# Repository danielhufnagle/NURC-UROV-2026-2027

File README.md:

# NURC-UROV-2026-2027
Electrical and Software for MATE UROV 2026-2027
well hello there

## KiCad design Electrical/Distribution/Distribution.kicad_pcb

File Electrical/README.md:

# Electrical

Place all PCB files here. Include both component and footprint libraries as well

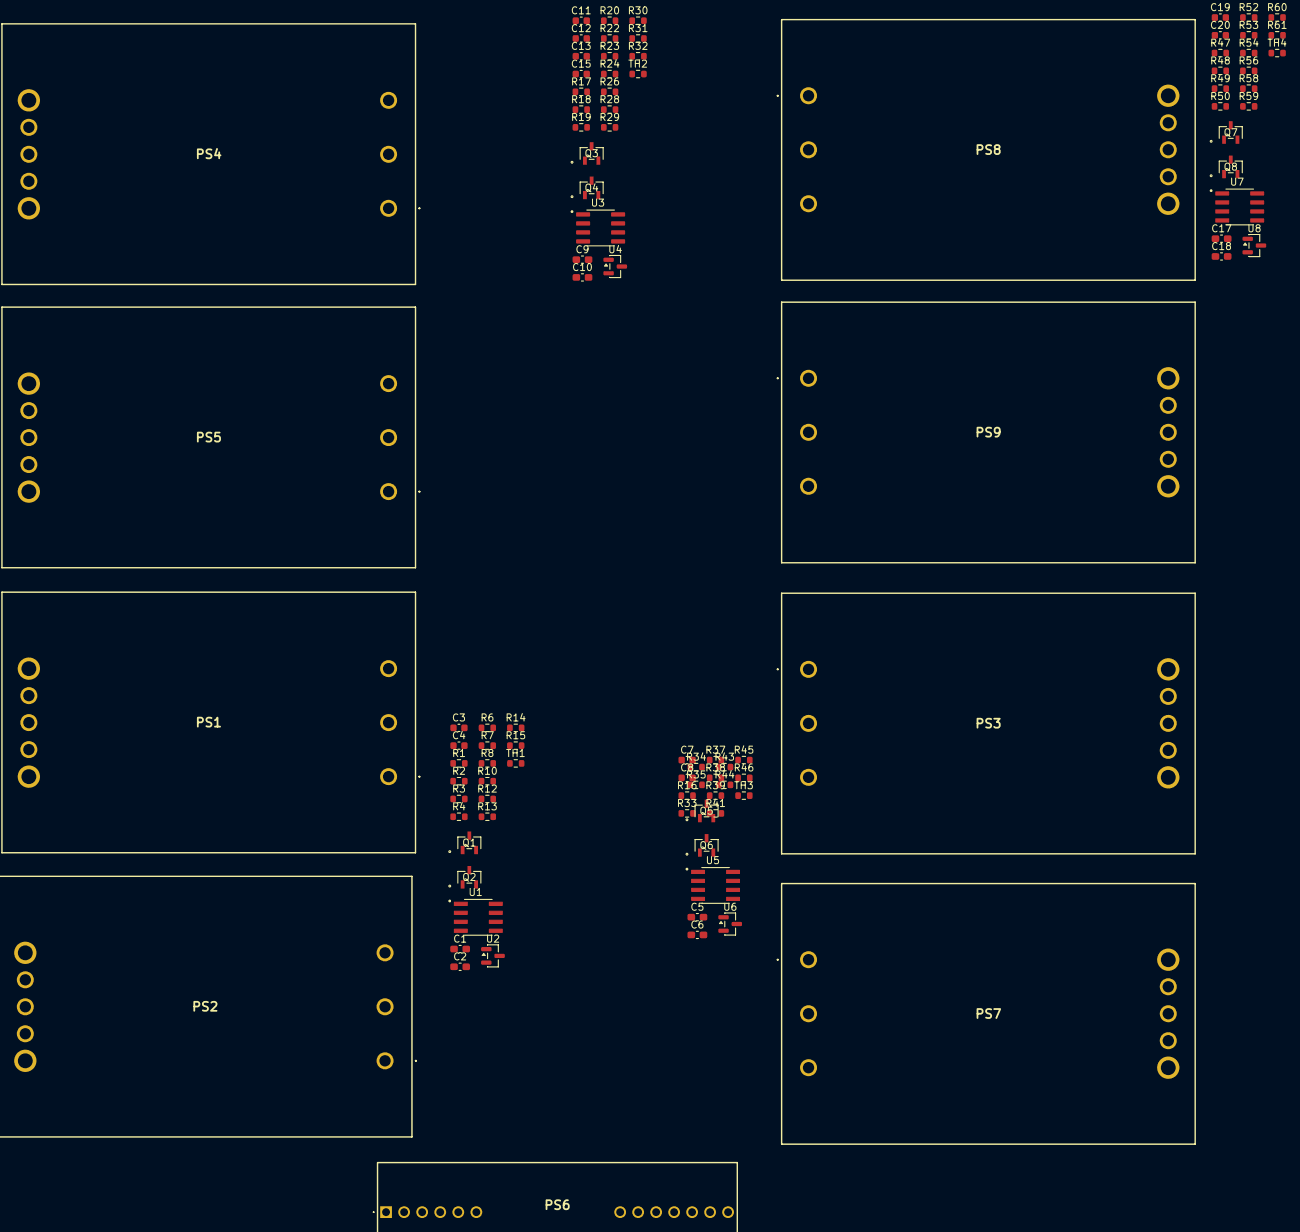
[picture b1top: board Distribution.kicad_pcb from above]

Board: 2 copper layers, 96 parts (0 on the bottom side), 48 nets, no tracks yet.

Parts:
C1, C2, C5, C6, C9, C10, C17, C18: 100uf; C_0603_1608Metric_Pad1.08x0.95mm_HandSolder
C3, C4, C7, C8, C11, C12, C19, C20: 100uf; C_0603_1608Metric
C13: 10uf; C_0603_1608Metric
C15: 100nF; C_0603_1608Metric
PS1, PS2, PS3, PS4, PS5, PS7, PS8, PS9: Q36SR12017NRFA
PS6: NID100-5; NID1005
Q1, Q2, Q3, Q4, Q5, Q6, Q7, Q8: Q_NMOS; TO-236AB_SOT23_NEX
R1, R3, R16, R17, R19, R34, R47, R49: 7k; R_0603_1608Metric
R2, R4, R13, R18, R20, R30, R33, R35, R44, R48, R50, R59: 5k; R_0603_1608Metric
R6, R7, R22, R23, R37, R38, R52, R53: 1k; R_0603_1608Metric
R8, R24, R39, R54: 50k; R_0603_1608Metric
R10, R12, R14, R15, R26, R28, R29, R31, R32, R41, R43, R45, R46, R56, R58, R60, R61: 10k; R_0603_1608Metric
TH1, TH2, TH3, TH4: Thermistor NTC 10k; R_0603_1608Metric
U1, U3, U5, U7: LM393; SOIC127P599X175-8N
U2, U4, U6, U8: LM4040DBZ-5; SOT-23

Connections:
/48-12-5/5VOut: PS6.1 (+VOUT_1), PS6.2 (+VOUT_2), PS6.3 (+VOUT_3), PS6.4 (+VOUT_4)
/48-12-5/5VRef: R22.1, R30.2, U3.8 (V+), U4.1 (K)
/48-12-5/12V: PS6.9 (+VIN_1), PS6.10 (+VIN_2)
/48-12-5/12V1: C11.2, PS4.8 (+VOUT), R19.1, R30.1, R31.1
/48-12-5/12V2: C12.2, PS5.8 (+VOUT), R17.1, R32.1
/48-12-5/48V1: C9.1, PS4.1 (+VIN)
/48-12-5/48V2: C10.1, PS5.1 (+VIN)
/48-12-5/CompOut1: R24.1, R26.2, U3.1
/48-12-5/ConvertersOn: PS4.2 (ON/OFF), PS5.2 (ON/OFF), PS6.13 (R.C.), R29.1
/48-12-5/Vtherm: R28.2, TH2.1
/48-12-5/~5Vin1: R19.2, R20.1
/48-12-5/~5Vin2: R17.2, R18.1
/48-12-inst1/5VRef: R6.1, R10.1, R13.2, U1.8 (V+), U2.1 (K)
/48-12-inst1/12V1: C3.2, PS1.8 (+VOUT), R3.1, R13.1, R14.1
/48-12-inst1/12V2: C4.2, PS2.8 (+VOUT), R1.1, R15.1
/48-12-inst1/48V: C1.1, C2.1, PS1.1 (+VIN), PS2.1 (+VIN)
/48-12-inst1/CompOut1: R8.1, R10.2, U1.1
/48-12-inst1/ConvertersOn: PS1.2 (ON/OFF), PS2.2 (ON/OFF)
/48-12-inst1/Vtherm: R12.2, TH1.1
/48-12-inst1/~5Vin1: R3.2, R4.1
/48-12-inst1/~5Vin2: R1.2, R2.1
/48-12-inst2/5VRef: R37.1, R41.1, R44.2, U5.8 (V+), U6.1 (K)
/48-12-inst2/12V1: C7.2, PS3.8 (+VOUT), R34.1, R44.1, R45.1
/48-12-inst2/12V2: C8.2, PS7.8 (+VOUT), R16.1, R46.1
/48-12-inst2/48V: C5.1, C6.1, PS3.1 (+VIN), PS7.1 (+VIN)
/48-12-inst2/CompOut1: R39.1, R41.2, U5.1
/48-12-inst2/ConvertersOn: PS3.2 (ON/OFF), PS7.2 (ON/OFF)
/48-12-inst2/Vtherm: R43.2, TH3.1
/48-12-inst2/~5Vin1: R34.2, R35.1
/48-12-inst2/~5Vin2: R16.2, R33.1
/48-12-inst3/5VRef: R52.1, R56.1, R59.2, U7.8 (V+), U8.1 (K)
/48-12-inst3/12V1: C19.2, PS8.8 (+VOUT), R49.1, R59.1, R60.1
/48-12-inst3/12V2: C20.2, PS9.8 (+VOUT), R47.1, R61.1
/48-12-inst3/48V: C17.1, C18.1, PS8.1 (+VIN), PS9.1 (+VIN)
/48-12-inst3/CompOut1: R54.1, R56.2, U7.1
/48-12-inst3/ConvertersOn: PS8.2 (ON/OFF), PS9.2 (ON/OFF)
/48-12-inst3/Vtherm: R58.2, TH4.1
/48-12-inst3/~5Vin1: R49.2, R50.1
/48-12-inst3/~5Vin2: R47.2, R48.1
GND: C1.2, C2.2, C3.1, C4.1, C5.2, C6.2, C7.1, C8.1, C9.2, C10.2, C11.1, C12.1, C13.2, C15.2, C17.2, C18.2, C19.1, C20.1, PS1.3 (-VIN), PS1.4 (-VOUT), PS2.3 (-VIN), PS2.4 (-VOUT), PS3.3 (-VIN), PS3.4 (-VOUT), PS4.3 (-VIN), PS4.4 (-VOUT), PS5.3 (-VIN), PS5.4 (-VOUT), PS6.5 (COM_1), PS6.6 (COM_2), PS6.7 (COM_3), PS6.8 (COM_4), PS7.3 (-VIN), PS7.4 (-VOUT), PS8.3 (-VIN), PS8.4 (-VOUT), PS9.3 (-VIN), PS9.4 (-VOUT), R2.2, R4.2, R18.2, R20.2, R29.2, R33.2, R35.2, R48.2, R50.2, TH1.2, TH2.2, TH3.2, TH4.2, U1.4 (V-), U2.2 (A), U3.4 (V-), U4.2 (A), U5.4 (V-), U6.2 (A), U7.4 (V-), U8.2 (A)
unnamed: R7.2, R8.2, U1.3 (+)
unnamed: R6.2, U1.2 (-)
unnamed: R23.2, R24.2, U3.3 (+)
unnamed: R22.2, U3.2 (-)
unnamed: R38.2, R39.2, U5.3 (+)
unnamed: R37.2, U5.2 (-)
unnamed: R53.2, R54.2, U7.3 (+)
unnamed: R52.2, U7.2 (-)

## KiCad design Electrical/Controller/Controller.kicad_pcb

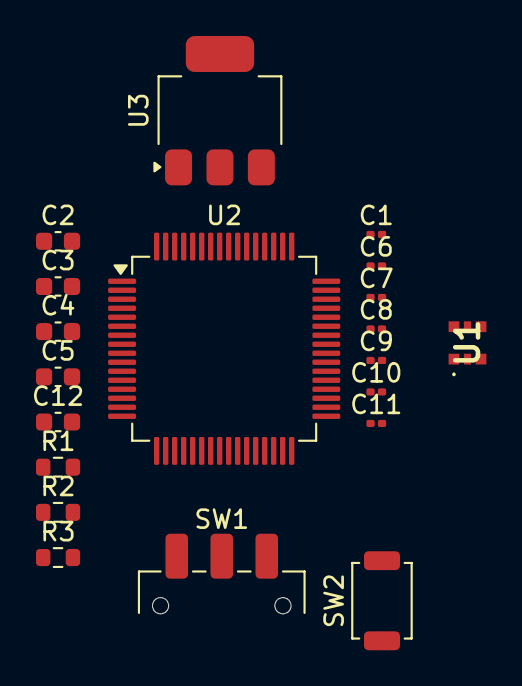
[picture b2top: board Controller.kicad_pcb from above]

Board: 2 copper layers, 20 parts (0 on the bottom side), 9 nets, no tracks yet.

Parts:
C1, C6, C7, C8, C9, C10, C11: 100nf; C_0201_0603Metric
C2, C3, C4: 10uf; C_0603_1608Metric
C5, C12: 100nf; C_0603_1608Metric
R1, R2, R3: 10k; R_0603_1608Metric
SW1: SW_SPDT; SW_SPDT_CK_JS102011SAQN
SW2: SW_SPST; SW_SPST_TS-1088-xR020
U1: 74LVC1G332; 74LVC1G332GW125
U2: STM32F446RETx; LQFP-64_10x10mm_P0.5mm
U3: AMS1117-3.3; SOT-223-3_TabPin2

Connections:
+5V: C4.1, U3.3 (VI)
/IsLeak: U1.4, U2.40 (PC9)
/LDO 3V3: C3.1, C6.1, C7.1, C8.1, C9.1, C10.1, C11.1, C12.2, R1.1, R3.1, U1.5 (VCC), U2.1 (VBAT), U2.13 (VDDA), U2.19 (VDD), U2.32 (VDD), U2.48 (VDD), U2.64 (VDD), U3.2 (VO)
GND: C1.2, C2.2, C3.2, C4.2, C5.1, C6.2, C7.2, C8.2, C9.2, C10.2, C11.2, C12.1, R2.2, SW2.1 (A), U1.2 (GND), U2.12 (VSSA), U2.18 (VSS), U2.31 (VSS), U2.47 (VSS), U2.63 (VSS), U3.1 (GND)
unnamed: R2.1, SW1.1 (A)
unnamed: C1.1, SW1.2 (B), U2.60 (BOOT0)
unnamed: R1.2, SW1.3 (C)
unnamed: C5.2, R3.2, SW2.2 (B), U2.7 (NRST)
unnamed: C2.1, U2.30 (VCAP_1)
